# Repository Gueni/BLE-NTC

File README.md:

# BLE NTC Temperature Sensor (NINA-B112)

Battery-powered Bluetooth LE temperature sensor built around the u-blox
NINA-B112 module (nRF52832). A Honeywell T7335 NTC probe sticks out of the
bottom of a Hammond 1553 handheld enclosure; the board charges its Li-Po cell
from micro-USB and reports the temperature over BLE.

| 3D view | 2D layout |
| --- | --- |
|  |  |

| Enclosure, open | Enclosure, bottom | Enclosure, side (NTC probe) |
| --- | --- | --- |
|  |  |  |

## On the board

| Ref | Part | Role |
| --- | --- | --- |
| U2 | NINA-B112-00B-00 | BLE module (nRF52832) |
| S1 | Honeywell T7335 D1008 | NTC temperature probe |
| U1 | MCP73831T-2ACI/MC | Single-cell Li-Po charger |
| J3 | Battery pads | Li-Po cell (`BAT+`, `BAT-`) |
| U4, L2 | TPS62132 + 2.2 µH (XAL5030) | Buck converter |
| J1, D2 | Amphenol GMCBA058211230HHR micro-USB + SMA6J5.0CA TVS | Charging input with surge protection |
| Q1 | NX3008NBK | N-MOSFET |
| D1 | Würth 150353M153300 | RGB status LED |
| S2 | E-Switch 800CSP1B6M6QE | SPDT push button |
| J2 | Würth 61300621121, 2×3 header | Programming header |

## Firmware

`firmware/` holds an nRF5 SDK project. `main.c` samples the NTC divider on
`AIN0` every 5 s, converts it to a temperature, and publishes it through a custom
BLE temperature service (`ble/ble_temp_service.c`) under the device name
`BLE-NTC`.

## Repository layout

```
0010_ble_ntc/
├── PCB/                               # Altium Designer project
│   ├── BLE-NTC.PrjPCB                 # Project file (open this)
│   ├── BLE-NTC.SchDoc                 # Schematic
│   ├── BLE-NTC.PcbDoc                 # PCB layout
│   ├── BLE-NTC.PCBDwf                 # Draftsman drawing
│   ├── OutJob.OutJob, BLE-NTC.OutJob  # Output jobs
│   └── Project Outputs for BLE-NTC/   # PDFs, BOM and STEP exports
├── mechanical/                        # SolidWorks enclosure (Hammond 1553AA)
│   ├── Assem2.SLDASM                  # Enclosure + PCB assembly
│   ├── Assem2 -nopcb.SLDASM           # Enclosure without the PCB
│   ├── Assembly_without_PCB.SLDDRW    # Assembly drawing
│   ├── *.SLDPRT                       # Enclosure, probe, switch, battery and screw models
│   └── drawings/                      # PDF export of the assembly drawing
├── firmware/                          # nRF5 SDK firmware
└── images/                            # Renders used in this README
```

## Component library

This repo stores no libraries. Every part comes from the general Altium library
in [Gueni/0000_libraries](https://github.com/Gueni/0000_libraries):

| File | Used for |
| --- | --- |
| [`Altium/DATABASE.DbLib`](https://github.com/Gueni/0000_libraries/blob/master/Altium/DATABASE.DbLib) | Database library the schematic components link to |
| [`Altium/DB.mdb`](https://github.com/Gueni/0000_libraries/blob/master/Altium/DB.mdb) | Parts database (part numbers, MPNs, suppliers) |
| [`Altium/SCH.SchLib`](https://github.com/Gueni/0000_libraries/blob/master/Altium/SCH.SchLib) | Schematic symbols |
| [`Altium/FTP.PcbLib`](https://github.com/Gueni/0000_libraries/blob/master/Altium/FTP.PcbLib) | PCB footprints and 3D models |

### Setup

The project finds the library through a relative path, so clone both repos side
by side in the same workspace folder:

```
WORKSPACE/
├── 0000_libraries/                   # git clone https://github.com/Gueni/0000_libraries.git
└── 0010_ble_ntc/                     # this repo
```

The project file references `..\..\0000_libraries\Altium\DATABASE.DbLib` and
adds `..\..\0000_libraries\Altium\` as a library search path. The DbLib's
database path is absolute (`D:\WORKSPACE\0000_libraries\Altium\DB.mdb`); see the
[library README](https://github.com/Gueni/0000_libraries#setup) if your
workspace lives elsewhere.

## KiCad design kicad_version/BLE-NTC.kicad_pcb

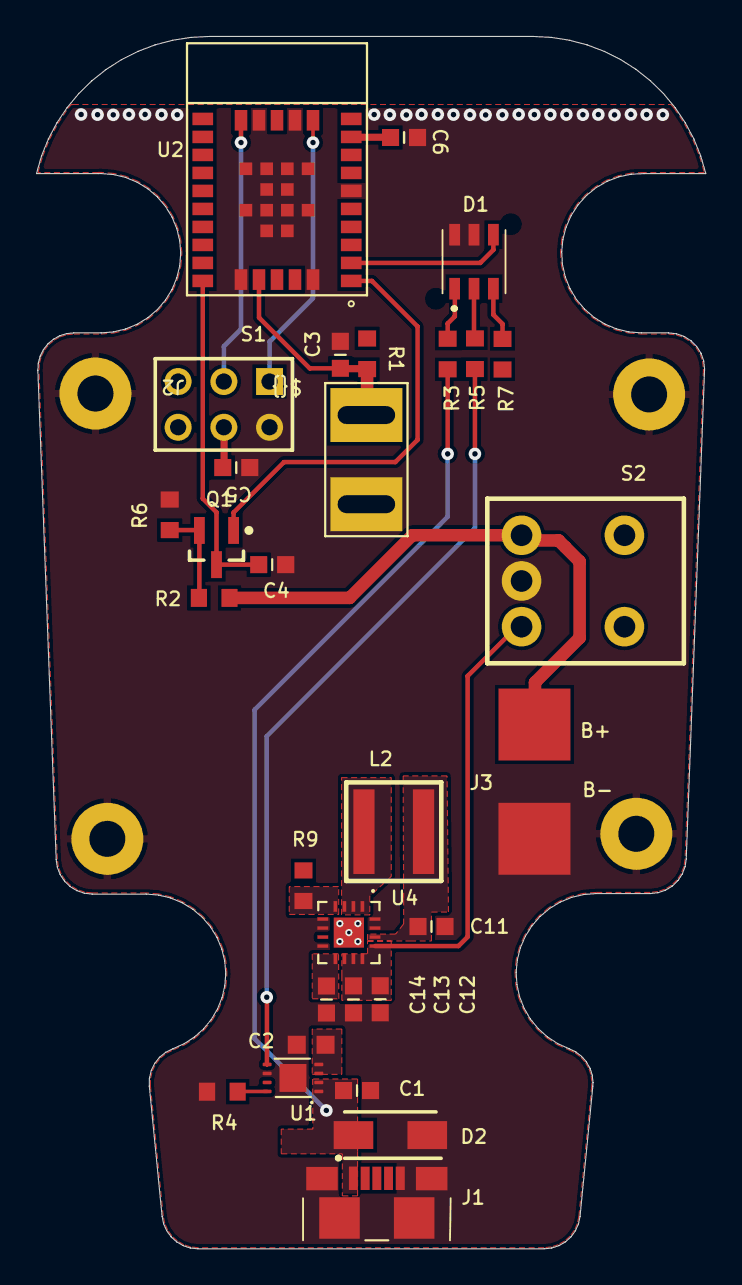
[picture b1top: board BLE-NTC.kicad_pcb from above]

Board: 2 copper layers, 37.2 x 67.4 mm, 30 parts (0 on the bottom side), 20 nets.

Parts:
C1, C2, C3, C4, C5, C6, C11, C12, C13, C14: Capacitor; CAPC1608N
D1: Red & Green & Blue, 120deg; 150353M153300
D2: SMA6J5.0CA-TR
J1: GMCBA058211230HHR
J2: 61300621121; HDR2X3
J3: BAT_PAD
L2: XAL5030-222MEB; 22uh-XAL5030
Q1: NX3008NBK; SOT23-3N
R1, R2, R3, R4, R5, R6, R7, R9: Resistor; RESC1608N
S1: T7335; T7335D
S2: 800CSP1B6M6QE
U1: MCP73831T-2ACI/MC; mcp-SON50P300X200X100-9N-D
U2: NINA-B112-00B-00; NINAB112
U4: TPS62132RGTR; tps62132

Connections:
3V3: C5.2, C6.2, C11.2, J2.4, L2.2, R1.2, R7.2, R9.2, U2.9, U2.10, U4.7, U4.14
5V: C1.1, D2.2, J1.1, R3.2, U1.1, U1.2
ADC_NTC: C3.2, R1.1, S1.1, U2.27
ADC_VBAT: C4.2, Q1.3, U2.25
GND: C1.2, C2.2, C3.1, C4.1, C5.1, C6.1, C11.1, C12.1, C13.1, C14.1, D1.2, D1.4, D2.1, J1.5, J1.6, J1.7, J1.8, J1.9, J2.2, J3.BAT-, R4.2, R6.2, S1.2, S2.2, U1.6, U1.9, U2.6, U2.12, U2.14, U2.26, U2.30, U2.31, U2.32, U2.33, U2.34, U2.35, U2.36, U2.37, U2.38, U2.39, U2.40, U2.41, U2.42, U4.5, U4.6, U4.8, U4.15, U4.16
LED_B: D1.6, U2.2
MOS: Q1.1, U2.1
NetC14_2: C14.2, U4.9
NetD1_1: D1.1, R3.1
NetD1_3: D1.3, R5.1
NetD1_5: D1.5, R7.1
NetL2_1: L2.1, U4.1, U4.2, U4.3
NetQ1_2: Q1.2, R2.1, R6.1
NetR4_1: R4.1, U1.8
NetR9_1: R9.1, U4.4
STAT: R5.2, U1.5
SWDCLK: J2.1, U2.11
SWDIO: J2.3, U2.15
VBAT+: C2.1, J3.BAT+, R2.2, S2.3, U1.3, U1.4
VBAT_TSP: C12.2, C13.2, S2.1, U4.10, U4.11, U4.12, U4.13

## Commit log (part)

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2025-05-13 ble sdk
2025-05-13 Remove obsolete Status Report file from PCB directory
2025-11-04 kicad version added
